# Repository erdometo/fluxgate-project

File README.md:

# 🧲 High-Precision Fluxgate Magnetic Field Sensor Design

An open-source, high-sensitivity, single-axis Fluxgate magnetometer and development platform designed for aerospace, geophysics, and navigation applications. This project implements a fully integrated system containing hardware (KiCad PCBs), firmware (MSP430 24-bit SD-ADC & RP2040 Controller), simulations (LTSpice), and software (Python PyQt real-time GUI).

Developed as a senior capstone engineering project at **Karadeniz Technical University (KTU)** by **Erdem Metin** and **Mücahit Ata**, under the supervision of **Prof. Dr. İsmail Kaya**.

---

## 📸 System Overview

The Fluxgate sensor system is designed around a dual-MCU architecture consisting of an **RP2040** (master controller and driver) and an **MSP430AFE253** (24-bit Sigma-Delta ADC data acquisition).

*Fig 1: Full system schematic diagram detailing all MCU pinouts, power distribution, and analog filters.*

*Fig 2: KiCad PCB 3D layout render (left) and the fully assembled physical testing board (right).*

```mermaid
graph TD
    PC[Computer PyQt GUI / Matlab] <-->|USB virtual COM / UDP Wifi| Pico[Raspberry Pi Pico RP2040]
    Pico -->|PWM Excitation Control f| FET[H-Bridge MOSFET Driver]
    FET -->|AC Excitation staircase Wave| Core[Magnetic Core & Coils]
    Core -->|Induced Sensing Signal| Demod[Analog Processing Circuit]
    Demod -->|DC Level / AC Signal| MSP[MSP430AFE253 24-bit ADC]
    MSP -->|1.5 MBaud UART| Pico
```

---

## 📖 Theory of Operation

A **Fluxgate Magnetometer** measures weak static or low-frequency magnetic fields (in the nT to µT range) by exploiting the non-linear magnetic saturation characteristics of a ferromagnetic core.

1. **Excitation (Drive):** An AC current at frequency $f$ drives the core deep into saturation in both positive and negative directions.
2. **Symmetric Core State:** In the absence of an external magnetic field, the magnetic flux changes symmetrically. The voltage induced in the sensing (pick-up) coil contains only **odd harmonics** ($3f$, $5f$, etc.).
3. **Asymmetric Core State (External Field Present):** When an external magnetic field (like the Earth's field $H_{ext}$) is present, it biases the core, causing it to saturate earlier in one direction and later in the other.
4. **Second Harmonic (2f) Detection:** This asymmetry generates **even harmonics** (predominantly the $2f$ component) in the sensing coil. The amplitude of this second harmonic is directly proportional to the magnitude of the external magnetic field, and its phase indicates the field's direction.

---

## 🛠️ Project Structure

The repository is structured into logically separated folders to make implementation and replication straightforward:

*   📁 **[`Hardware/`](file:///c:/Users/ASUS/Desktop/Fluxgate/Fluxgate-Project-Files/Hardware)**: KiCad schematic and PCB layout designs, Gerber files, and Bill of Materials (BOM).
*   📁 **[`Firmware/`](file:///c:/Users/ASUS/Desktop/Fluxgate/Fluxgate-Project-Files/Firmware)**:
    *   **MSP430:** IAR and CCS projects for 24-bit Sigma-Delta ADC sampling at 16.5 kSps and 1.5 MBaud USART transmission.
    *   **RP2040 (Raspberry Pi Pico):** C/C++ SDK projects generating precise excitation PWM and streaming data to PC via USB Serial or UDP Wi-Fi.
*   📁 **[`Software/`](file:///c:/Users/ASUS/Desktop/Fluxgate/Fluxgate-Project-Files/Software)**: Python-based GUI utilizing `pyqtgraph` for real-time serial and UDP plotting, and Matlab analytics.
*   📁 **[`Simulations/`](file:///c:/Users/ASUS/Desktop/Fluxgate/Fluxgate-Project-Files/Simulations)**: LTSpice circuits simulating the H-Bridge excitation driver and the analog synchronous demodulation path.

---

## 🚀 Step-by-Step Build & Replication Guide

To replicate and build this high-precision Fluxgate sensor, follow these five steps:

### 1. Hardware Fabrication & Assembly
1. Go to **[`Hardware/`](file:///c:/Users/ASUS/Desktop/Fluxgate/Fluxgate-Project-Files/Hardware)** and select either the **Excitation Circuit V1**, the **Excitation Circuit Final**, or the **JLCPCB Version** which is optimized for SMT assembly.
2. Export Gerbers or use the provided `.zip` files under the directories to order PCBs from your manufacturer (e.g., JLCPCB).
3. Assemble the PCB using the BOM. Key components include:
    *   **Primary Controller:** Raspberry Pi Pico (RP2040)
    *   **Precision ADC:** MSP430AFE253IPW (24-bit Sigma-Delta ADC)
    *   **H-Bridge Driver:** HIP4082xB half-bridge gate driver
    *   **Excitation MOSFETs:** AP2300 or IRFZ44N
    *   **Ultra Low-Noise Opamps:** TP2311 or LT149x series (12nV/√Hz input noise)
    *   **Voltage References:** AN431 shunt regulators (2.5V, 20ppm/°C stability)

### 2. Fluxgate Core & Coil Preparation
1. **Core Selection:** Use a high-permeability **green iron-powder ferrite toroid core** with an **inner diameter of 7 mm, thickness of 2 mm, and height of 4.5 mm**. (While a 6-81 Permalloy racetrack core with $100\text{ µm}$ laminations provides lower noise, a toroidal ferrite core is robust and hand-windable).
2. **Drive Winding:** Wind the excitation (drive) coil uniformly around the toroid using **32 AWG** enameled copper wire. In the experimental prototype, the completed drive winding exhibited a measured **series resistance of $17.945\text{ }\Omega$** and a **series inductance of $19.686\text{ mH}$**.
3. **Sense Winding:** Wind the sensing (pick-up) coil on top of the drive winding, orienting the windings to capture the fluxgate effect while canceling direct coupling from the excitation drive.

*Fig 3: The custom hand-wound toroidal fluxgate core integrated onto the testing board.*

### 3. Simulation & Validation
1. Open **[`Simulations/LTSpice/`](file:///c:/Users/ASUS/Desktop/Fluxgate/Fluxgate-Project-Files/Simulations)**.
2. Run `fluxgate.asc` to simulate the H-Bridge excitation path. Verify the staircase voltage waveform across the drive bobbin.
3. Run `fluxgateACAnaliz.asc` or `Draft7.asc` to analyze the frequency response of the active integrator and synchronous demodulator. Ensure the integration region lies between **159 Hz and 1591 Hz** and the low-pass filter kesim frekansı is configured near **28 Hz**.

### 4. Firmware Deployment
1. **MSP430 Firmware:**
    *   Open IAR Embedded Workbench or Code Composer Studio.
    *   Load the project in **[`Firmware/MSP430_AFE_ADC/`](file:///c:/Users/ASUS/Desktop/Fluxgate/Fluxgate-Project-Files/Firmware/MSP430_AFE_ADC)** or **[`Firmware/MSP430_ADC_to_UART/`](file:///c:/Users/ASUS/Desktop/Fluxgate/Fluxgate-Project-Files/Firmware/MSP430_ADC_to_UART)**.
    *   Compile and flash the firmware using an eZ-FET debugger (or the Spy-Bi-Wire pins on an MSP430 Launchpad).
    *   *Function:* Configures the 12MHz MCLK, initializes the SD24 Module in group conversion mode, and streams 24-bit raw ADC readings via USART0 at **1.5M Baud**.
2. **RP2040 Firmware:**
    *   Navigate to **[`Firmware/Pico_Firmwares/`](file:///c:/Users/ASUS/Desktop/Fluxgate/Fluxgate-Project-Files/Firmware/Pico_Firmwares)**.
    *   Choose either `pico-custom-firmware-usb` (USB Virtual Serial) or `pico-custom-firmware-udp` (Wi-Fi streaming).
    *   Build the project using the Pico SDK (`CMake`) and flash the resulting `.uf2` file onto your Pi Pico.
    *   *Function:* Emits precise complementary PWM drive signals (80µs duty, 40µs dead-time) at frequency $f$ to drive the H-Bridge. It uses a **PIO state machine** to reliably capture the 1.5MBaud UART stream from the MSP430 and forwards it to the PC.

### 5. GUI & Visualization
1. Install Python 3 and requirements:
   ```bash
   pip install pyqtgraph PyQt5 pyserial numpy
   ```
2. Run the visualization app in **[`Software/Python_GUI_Demo/`](file:///c:/Users/ASUS/Desktop/Fluxgate/Fluxgate-Project-Files/Software/Python_GUI_Demo)**:
   ```bash
   python compass.py
   # or
   python pyqtgraph_float_v2x2_yesim.py
   ```
3. Connect your Pi Pico to the PC via USB. You will see a real-time rolling graph of the 24-bit sampled magnetic field data representing the external field.

---

## 📡 Digital Signal Processing (DSP) & Digital Lock-In Mode

During the final experimental testing phase of this project, the analog op-amps in the physical synchronous demodulation circuit were found to be defective or counterfeit, preventing analog phase detection from working out of the box. To solve this, the project utilized a highly robust **Digital Signal Processing (DSP)** pipeline to bypass the analog demodulator entirely.

### Bypassing the Analog Demodulator
1. The analog SPDT switch (SN74LVC1G3157) was disabled (tied to a static ground state via the MCU).
2. The active low-noise op-amps were configured as a simple differential preamplifier.
3. The raw, high-speed AC signal (which contains the even and odd harmonics) was fed directly into the **MSP430's 24-bit Sigma-Delta ADC**.
4. The raw, un-demodulated samples were digitized at ~16.5 kSps and streamed to the PC via the RP2040 UART/USB bridge.

### Two Host-Side Digital Processing Implementations
Your software repository implements two distinct mathematical approaches on the host PC to extract the external magnetic field from this raw stream:

1. **Frequency-Domain Demodulation (Real-Time FFT):**
   * *File:* **[`pyqtgraph_float_v2x2_yesim.py`](file:///c:/Users/ASUS/Desktop/Fluxgate/Fluxgate-Project-Files/Software/Python_GUI_Demo/pyqtgraph_float_v2x2_yesim.py)**
   * *Method:* Computes a high-performance **Fast Fourier Transform (FFT)** on blocks of 8192 raw samples using Scipy:
     ```python
     Yf0 = fft(ch0)
     ```
   * *Result:* The GUI displays the real-time frequency spectrum. By measuring the amplitude peak of the **second harmonic ($2f$ at 25 kHz)** in the frequency domain, the software calculates the precise external magnetic field intensity, completely replacing the physical analog lock-in filters!

2. **Time-Domain Smoothing (Moving Average Convolution):**
   * *Files:* **[`udp_plot_pyqt.py`](file:///c:/Users/ASUS/Desktop/Fluxgate/Fluxgate-Project-Files/Software/Python_GUI_Demo/udp_plot_pyqt.py)** and **[`udp_plot_pyqt_2.py`](file:///c:/Users/ASUS/Desktop/Fluxgate/Fluxgate-Project-Files/Software/Python_GUI_Demo/udp_plot_pyqt_2.py)**
   * *Method:* Unpacks the high-speed telemetry and applies a real-time **Moving Average Filter** using NumPy convolution across a 1000-sample window:
     ```python
     filtered_data = np.convolve(data, weights, mode='valid')
     ```
   * *Result:* Smooths out the excitation switching ripples and transient spikes, feeding a clean time-domain signal to the graphical compass needle interface to dynamically show the core's magnetic orientation.

---

## 🛠️ Hardware Debugging & Engineering Solutions

During the assembly and testing phase, two critical engineering challenges arose and were systematically resolved:

### 1. The H-Bridge Bootstrap Capacitor & Duty Cycle Adaptation
*   **The Issue:** High-side gate drivers require a bootstrap capacitor ($C_{Bst}$) to maintain the gate-to-source voltage ($V_{GS}$) when the high-side MOSFET turns on. By design guidelines, the minimum bootstrap capacitance is:
    $$C_{Bst} = \frac{Q_{gate}}{\Delta V_{Bst}}$$
    Using the AP2300 gate charge $Q_{gate} = 11\text{ nC}$ and an acceptable voltage ripple $\Delta V_{Bst} = 0.1\text{ V}$, the minimum capacitor required is $110\text{ nF}$. Due to a design oversight, a **$1\text{ nF}$** capacitor was initially populated. This capacitor discharged instantly, causing the high-side gate drivers to drop out immediately.
*   **The Fix:** Populating a **$1\text{ µF}$** capacitor resolved the gate-dropout issue. However, experimental tests under a $330\text{ }\Omega$ load revealed that the high-side gate could remain continuously open for a maximum of **$1.125\text{ ms}$** before the bootstrap charge depleted.
*   **PWM Adaptation:** To prevent the high-side gate from collapsing during lower frequencies, the RP2040 firmware was adapted to emit a highly optimized PWM excitation pattern. Instead of a basic symmetrical square wave, the drive cycle was structured as:
    *   **$0.8\text{ ms}$ Positive Drive Phase** (containing high-speed $80\text{ µs}$ pulses with $40\text{ µs}$ dead-times).
    *   **$0.4\text{ ms}$ Neutral Phase** (H-bridge disabled, allowing the bootstrap capacitors to fully recharge).
    *   **$0.8\text{ ms}$ Negative Drive Phase** (H-bridge reversed).

### 2. Defective Analog Op-Amps & DSP Bypass
*   **The Issue:** During board validation, short-circuiting the sensing coil to ground resulted in the low-noise differential preamplifier and active integrator output locks stuck at a solid **$2.5\text{ V}$** (the virtual ground analog reference voltage). The op-amps (TP2311 or LT1492) failed to respond to any AC or DC input signal changes, leading to the conclusion that the physical components received were defective or counterfeit.
*   **The Solution:** The analog synchronous SPDT demodulator switch (SN74LVC1G3157) was set to ground mode via the RP2040, transforming the first stage into a simple, highly linear $1:2$ differential preamplifier (total differential gain of 20). The raw, high-speed AC pick-up signal was routed directly into the MSP430's 24-bit Sigma-Delta ADC, and the entire lock-in and filtering cascade was bypassed in hardware and reconstructed in real-time software on the host PC.

---

## ⚡ Specifications

| Parameter | Value | Description |
| :--- | :--- | :--- |
| **Sensor Type** | Parallel Fluxgate | Single Axis Magnetometer |
| **Excitation Waveform** | AC Staircase Wave | Minimizes transient EMF spikes |
| **Excitation Frequency** | 12.5 kHz | Configurable via Pico PWM registers |
| **ADC Resolution** | 24-Bit | Sigma-Delta Converter (MSP430AFE253) |
| **Sampling Rate** | ~16,500 samples/sec | High-speed oversampled stream |
| **Baud Rate** | 1,500,000 Baud | High-speed MSP430 to RP2040 UART link |
| **Demodulator Gain** | 1:10 (or 20 Differential) | Synchronous analog SPDT demodulation |
| **Low-Pass Filter (LPF)** | $f_c = 28.42\text{ Hz}$ | Eliminates grid noise (50Hz) and ripples |
| **Integrator Bandwidth** | 159 Hz to 1591 Hz | Limits noise and captures second harmonics |

---

## ⚖️ License

This project is open-source and released under the [MIT License](file:///c:/Users/ASUS/Desktop/Fluxgate/Fluxgate-Project-Files/LICENSE). Feel free to use, modify, and distribute for personal, academic, or commercial purposes.

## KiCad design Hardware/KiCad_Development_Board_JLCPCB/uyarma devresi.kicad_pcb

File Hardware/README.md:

# 🔌 Hardware & PCB Design

This folder contains the KiCad schematics and PCB layout files for the Fluxgate Sensor Development and Testing Board. The hardware combines the master controller, excitation power electronics, high-speed 24-bit ADC, and a low-noise analog signal processing path into a single 150mm x 100mm PCB.

*Fig 1: Complete circuit schematic for the Fluxgate Development Board (open-source).*

*Fig 2: KiCad board layout 3D render (left) and the actual manufactured PCB received from JLCPCB (right).*

---

## 📁 Directory Directory

*   📁 **[`Excitation_Circuit_V1/`](file:///c:/Users/ASUS/Desktop/Fluxgate/Fluxgate-Project-Files/Hardware/Excitation_Circuit_V1)**: The initial KiCad prototype.
*   📁 **[`Excitation_Circuit_Final/`](file:///c:/Users/ASUS/Desktop/Fluxgate/Fluxgate-Project-Files/Hardware/Excitation_Circuit_Final)**: The revised KiCad project with improvements in the bootstrap driver and ground isolation.
*   📁 **[`KiCad_Development_Board_JLCPCB/`](file:///c:/Users/ASUS/Desktop/Fluxgate/Fluxgate-Project-Files/Hardware/KiCad_Development_Board_JLCPCB)**: Design optimized for JLCPCB's automated surface mount technology (SMT) assembly service. Contains BOM and component positioning files.

---

## ⚡ Hardware Architecture & Circuit Sub-systems

The Fluxgate Development Board contains four main hardware sub-systems:

### 1. Power Management & Low-Noise Rails
Since magnetic sensors are highly sensitive to power supply noise, a robust voltage regulation and reference system is implemented:
*   **Main Regulator:** AMS1117-3.3 produces the digital 3.3V supply.
*   **Negative Rail Generator:** ME7660C charge-pump voltage converter generates a low-noise $-3.3\text{ V}$ rail from the $3.3\text{ V}$ input.
*   **Precision Analog References:** Originally, the op-amps shared the noisy 3.3V digital rail with the microcontrollers, which coupled massive MCU switching ripples into the analog signal path. To achieve extremely low-noise operation, the board was modified to use two **AN431 precision shunt regulators** with a **20 PPM/°C temperature coefficient**. These regulators derive highly stable $+2.5\text{ V}$ and $-2.5\text{ V}$ virtual ground references from the noisy $3.3\text{ V}$ rail, isolated via $10\text{ }\Omega$ current-limiting resistors to prevent temperature-induced offset drifts.

```
       [ 5V USB Input ]
              │
      ┌───────┴───────┐
      ▼               ▼
[AMS1117-3.3V]   [ME7660C]
      │               │
  [ +3.3V ]       [ -3.3V ]
      │               │
  [ AN431 ]       [ AN431 ]
      │               │
  [ +2.5V ]       [ -2.5V ]
```

### 2. Excitation Drive (H-Bridge)
To saturate the ferromagnetic core in both directions:
*   **Drivers:** Two half-bridge drivers (LP1111) are configured to form a full H-bridge.
*   **Switching Elements:** Low $R_{DS(on)}$ AP2300 or IRFZ44N N-channel MOSFETs.
*   **Protection:** 1N5400 flyback diodes protect the MOSFETs against massive back-EMF spikes (up to 200A instantaneous rating) when the coil current reverses.
*   **Bootstrap Optimization:** High-side gate drivers require a bootstrap capacitor ($C_{Bst}$) to maintain the gate-to-source voltage ($V_{GS}$) when the high-side MOSFET is active. The minimum bootstrap capacitance is calculated using:
    $$C_{Bst} = \frac{Q_{gate}}{\Delta V_{Bst}}$$
    Using the AP2300 gate charge $Q_{gate} = 11\text{ nC}$ and an acceptable voltage ripple $\Delta V_{Bst} = 0.1\text{ V}$, the minimum capacitor required is $110\text{ nF}$.
    *   Due to a design oversight, a **$1\text{ nF}$** capacitor was initially populated, causing the high-side MOSFETs to fail to switch completely.
    *   Replacing this with a **$94\text{ nF}$** capacitor allowed switching but triggered rapid charge depletion, causing the gates to turn on and off hundreds of times during a 5ms cycle.
    *   Restoring this to **$1\text{ µF}$** in the final hardware stabilized the gate, allowing stable gate-on periods up to **$1.125\text{ ms}$** under a $330\text{ }\Omega$ load.

### 3. Low-Noise Analog Signal Processing
The induced voltage from the pickup (sensing) coil undergoes analog preprocessing to extract the second harmonic component ($2f$):
*   **Differential Input Preamp:** Winding coupling experiences massive Common-Mode coupling from the high-voltage excitation drive. To solve this, the sensing coil is connected to a **differential preamplifier with a 1:2 gain** using low-noise TP2311 or LT1492 op-amps. This rejects common-mode excitation noise while increasing the differential sensing signal, bringing the total channel gain to 20.
*   **Synchronous Demodulator:** An SN74LVC1G3157 analog SPDT switch acts as a phase-sensitive rectifier. It is toggled by the RP2040 at twice the excitation frequency ($2f$), demodulating the second harmonic directly to DC.
*   **Active Integrator:** A low-pass integrator with an integration bandwidth configured between **159 Hz and 1591 Hz** ($\text{BW} = 1/(2\pi R_f C)$ with $R_f = 100\text{ k}\Omega, C = 10\text{ nF}$).
*   **Output Filter:** An RC low-pass filter with a cutoff frequency $f_c = 28.42\text{ Hz}$ ($C = 100\text{ nF}, R = 56\text{ k}\Omega$) filters out the $50\text{ Hz}$ mains grid noise and lingering switching ripples.

### 4. Precision Digitization & Processing
*   **MSP430AFE253:** Reads the filtered DC level (or the pre-demodulated high-speed AC signal) using its internal **24-bit Sigma-Delta ADC**. It runs on a $12\text{ MHz}$ internal DCO and transmits over UART at **1.5M Baud**.
*   **RP2040 (Raspberry Pi Pico):** Controls H-Bridge timing and routes the MSP430's digitized telemetry to a computer via USB virtual serial or a UDP socket over Wi-Fi.

---

## 📋 Component Checklist (BOM)

If assembling the board manually, ensure the following core components are ready:

| Designator | Component Name | Package | Description |
| :--- | :--- | :--- | :--- |
| **U5** | Raspberry Pi Pico | Module | Master controller and PWM driver |
| **U4** | MSP430AFE253IPW | TSSOP-24 | 24-Bit Sigma-Delta ADC / High-Speed DSP |
| **U1, U2** | LP1111 (or HIP4082) | SOIC-8 | Half-Bridge Bootstrap MOSFET Gate Drivers |
| **Q1 - Q4** | AP2300 (or IRFZ44N) | SOT-23 / TO-220 | Excitation H-Bridge Switching MOSFETs |
| **U3, U8, U9** | TP2311 (or LT1492) | SOIC-8 | $12\text{ nV}/\sqrt{\text{Hz}}$ Low-Noise Precision Op-Amps |
| **U12** | SN74LVC1G3157 | SOT-363 | High-Speed SPDT Analog Switch (Demodulator) |
| **U10, U11** | AN431 | SOT-23 | High-Precision Shunt Voltage Regulator (2.5V) |
| **U6** | ME7660C | SOIC-8 | Switched-Capacitor Negative Voltage Converter |
| **U7** | AMS1117-3.3 | SOT-223 | $3.3\text{ V}$ Low-Dropout Linear Regulator |
| **D1 - D4** | 1N5400 (or 1N4148) | DO-201AD | 200A Flyback Back-EMF Protection Diodes |

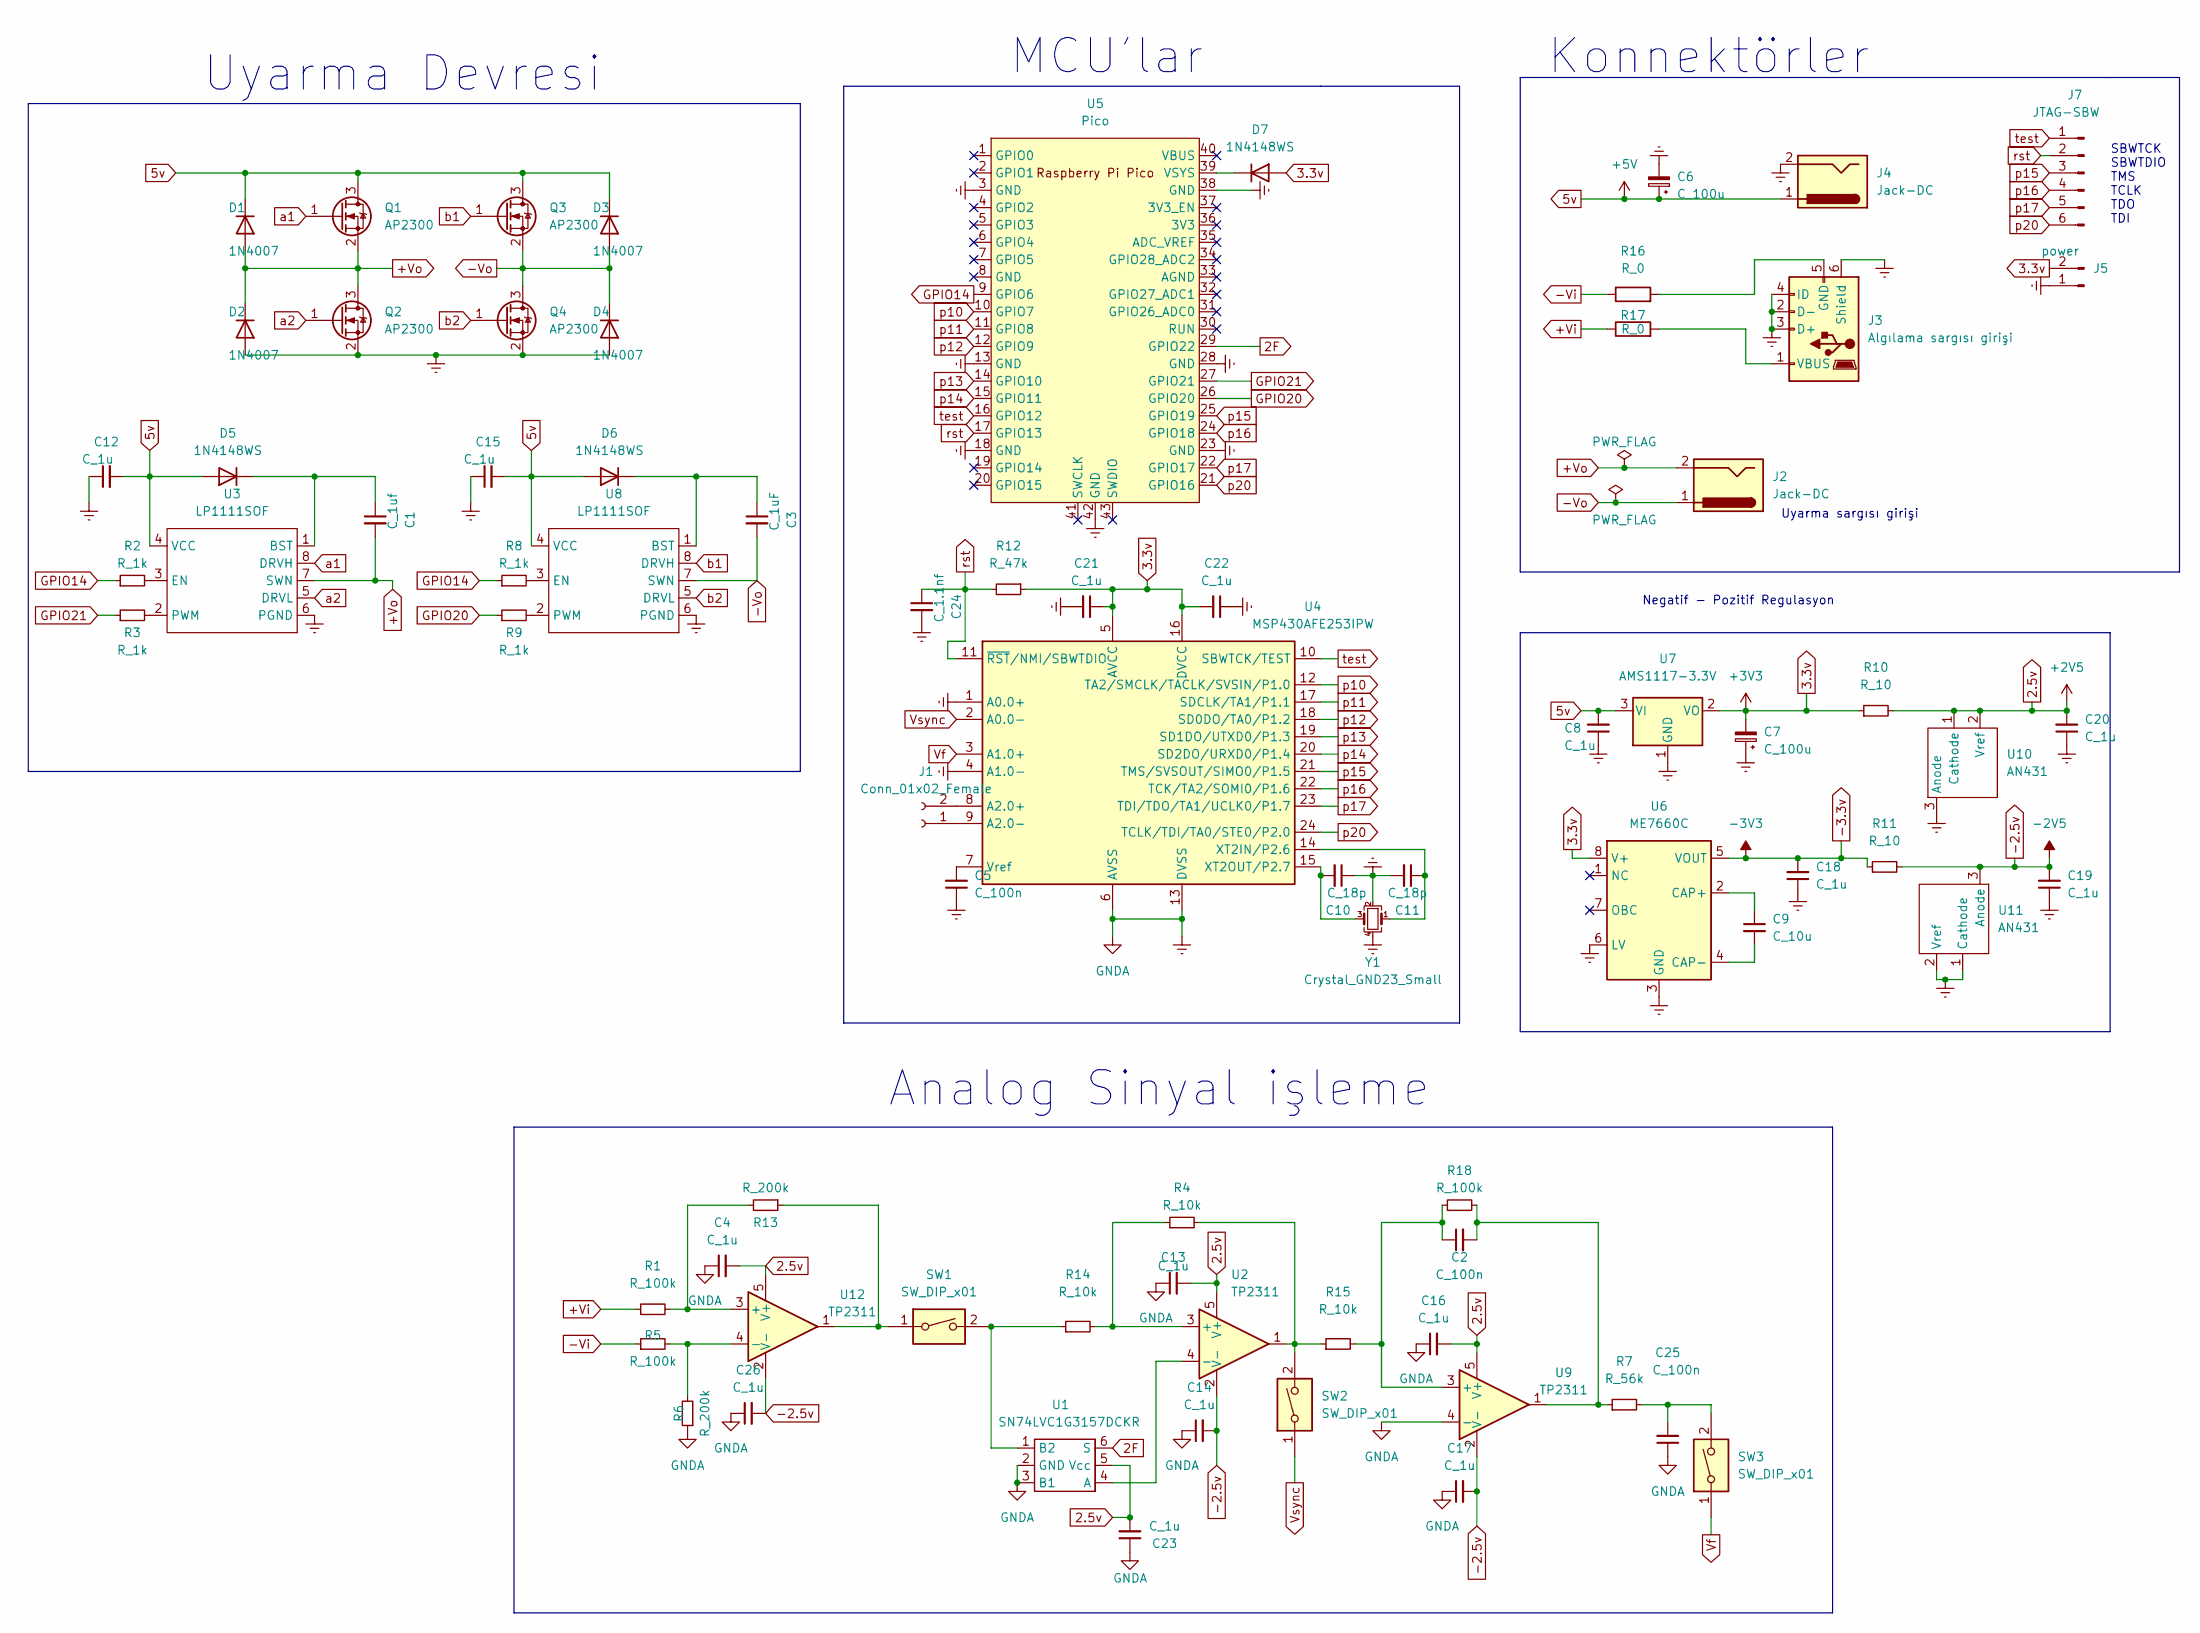
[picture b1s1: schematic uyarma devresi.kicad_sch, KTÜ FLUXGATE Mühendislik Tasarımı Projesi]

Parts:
C1: C_1uf; C_0402_1005Metric
C2, C5, C25: C_100n; C_0402_1005Metric
C3: C_1uF; C_0402_1005Metric
C4, C8, C12, C13, C14, C15, C16, C17, C18, C19, C20, C21, C22, C23, C26: C_1u; C_0402_1005Metric
C6, C7: C_100u; C_1206_3216Metric
C9: C_10u; C_0402_1005Metric
C10, C11: C_18p; C_0402_1005Metric
C24: C_1.1nf; C_0402_1005Metric
D1, D2, D3, D4: 1N4007; D_SOD-123F
D5, D6, D7: 1N4148WS; D_SOD-323
J1: Conn_01x02_Female; PinHeader_1x02_P2.54mm_Vertical
J2, J4: Jack-DC; BarrelJack_GCT_DCJ200-10-A_Horizontal
J3: Algılama sargısı girişi; USB_Micro-B_Molex-105017-0001
J5: power; PinHeader_1x02_P2.54mm_Vertical
J7: JTAG-SBW; PinHeader_1x06_P2.54mm_Vertical
Q1, Q2, Q3, Q4: AP2300; TSOT-23
R1, R5, R18: R_100k; R_0402_1005Metric
R2, R3, R8, R9: R_1k; R_0402_1005Metric
R4, R14, R15: R_10k; R_0402_1005Metric
R6, R13: R_200k; R_0402_1005Metric
R7: R_56k; R_0402_1005Metric
R10, R11: R_10; R_1206_3216Metric
R12: R_47k; R_0402_1005Metric
R16, R17: R_0; R_1206_3216Metric
SW1, SW2, SW3: SW_DIP_x01; SW_DIP_SPSTx01_Slide_6.7x4.1mm_W7.62mm_P2.54mm_LowProfile
U1: SN74LVC1G3157DCKR; Texas_R-PDSO-G6
U2, U9, U12: TP2311; SOT-23-5
U3, U8: LP1111SOF; SOP-8-1EP_4.57x4.57mm_P1.27mm_EP4.57x4.45mm
U4: MSP430AFE253IPW; TSSOP-24_4.4x7.8mm_P0.65mm
U5: Pico; RPi_Pico_SMD_TH
U6: ME7660C; SOP-8-1EP_4.57x4.57mm_P1.27mm_EP4.57x4.45mm
U7: AMS1117-3.3V; SOT-223-3_TabPin2
U10, U11: AN431; SOT-23
Y1: Crystal_GND23_Small; Crystal_SMD_3225-4Pin_3.2x2.5mm

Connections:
2.5v: C4.2, C13.2, C16.2, C20.2, C23.2, R10.2, U1.5 (Vcc), U2.5 (V+), U9.5 (V+), U10.1 (Cathode), U10.2 (Vref), U12.5 (V+)
2F: U1.6 (S), U5.29 (GPIO22)
3.3v: C7.2, C21.1, C22.2, D7.2 (A), J5.2, R10.1, R12.1, U4.5 (AVCC), U4.16 (DVCC), U6.8 (V+), U7.2 (VO)
5v: C6.1, C8.2, C12.2, C15.2, D1.1 (K), D3.1 (K), D5.2 (A), D6.2 (A), J4.1, Q1.3 (D), Q3.3 (D), U3.4 (VCC), U7.3 (VI), U8.4 (VCC)
+Vi: R1.1, R17.1
+Vo: C1.2, D1.2 (A), D2.1 (K), J2.2, Q1.2 (S), Q2.3 (D), U3.7 (SWN)
-2.5v: C14.2, C17.2, C19.2, C26.2, R11.2, U2.2 (V-), U9.2 (V-), U11.3 (Anode), U12.2 (V-)
-3.3v: C18.2, R11.1, U6.5 (VOUT)
-Vi: R5.1, R16.1
-Vo: C3.2, D3.2 (A), D4.1 (K), J2.1, Q3.2 (S), Q4.3 (D), U8.7 (SWN)
Earth: C4.1, C5.1, C6.2, C7.1, C8.1, C10.1, C11.2, C12.1, C13.1, C14.1, C15.1, C16.1, C17.1, C18.1, C19.1, C20.1, C21.2, C22.1, C23.1, C24.2, C25.1, C26.1, D2.2 (A), D4.2 (A), J3.2 (D-), J3.3 (D+), J3.4 (ID), J3.6 (Shield), J4.2, J5.1, Q2.2 (S), Q4.2 (S), R6.1, U1.2 (GND), U1.3 (B1), U3.6 (PGND), U4.1 (A0.0+), U4.4 (A1.0-), U4.6 (AVSS), U4.13 (DVSS), U5.3 (GND), U5.13 (GND), U5.18 (GND), U5.23 (GND), U5.28 (GND), U5.38 (GND), U5.42 (GND), U6.3 (GND), U6.6 (LV), U7.1 (GND), U8.6 (PGND), U9.4 (-), U10.3 (Anode), U11.1 (Cathode), U11.2 (Vref), Y1.2, Y1.4
GPIO14: R2.1, R8.1, U5.9 (GPIO6)
GPIO20: R9.1, U5.26 (GPIO20)
GPIO21: R3.1, U5.27 (GPIO21)
unnamed: C1.1, D5.1 (K), U3.1 (BST)
unnamed: C2.1, R15.2, R18.1, U9.3 (+)
unnamed: C2.2, R7.1, R18.2, U9.1
unnamed: C3.1, D6.1 (K), U8.1 (BST)
unnamed: C5.2, U4.7 (Vref)
unnamed: C9.1, U6.2 (CAP+)
unnamed: C9.2, U6.4 (CAP-)
unnamed: C10.2, U4.15 (XT2OUT/P2.7), Y1.3
unnamed: C11.1, U4.14 (XT2IN/P2.6), Y1.1
unnamed: C25.2, R7.2, SW3.2
unnamed: J1.1, U4.9 (A2.0-)
unnamed: J1.2, U4.8 (A2.0+)
unnamed: J3.1 (VBUS), R17.2
unnamed: J3.5 (GND), R16.2
unnamed: R1.2, R13.2, U12.3 (+)
unnamed: R2.2, U3.3 (EN)
unnamed: R3.2, U3.2 (PWM)
unnamed: R4.1, R14.2, U2.3 (+)
unnamed: R4.2, R15.1, SW2.2, U2.1
unnamed: R5.2, R6.2, U12.4 (-)
unnamed: R8.2, U8.3 (EN)
unnamed: R9.2, U8.2 (PWM)
unnamed: R13.1, SW1.1, U12.1
unnamed: R14.1, SW1.2, U1.1 (B2)
unnamed: U1.4 (A), U2.4 (-)
unnamed: D7.1 (K), U5.39 (VSYS)
Vf: SW3.1, U4.3 (A1.0+)
Vsync: SW2.1, U4.2 (A0.0-)
a1: Q1.1 (G), U3.8 (DRVH)
a2: Q2.1 (G), U3.5 (DRVL)
b1: Q3.1 (G), U8.8 (DRVH)
b2: Q4.1 (G), U8.5 (DRVL)
p10: U4.12 (TA2/SMCLK/TACLK/SVSIN/P1.0), U5.10 (GPIO7)
p11: U4.17 (SDCLK/TA1/P1.1), U5.11 (GPIO8)
p12: U4.18 (SD0DO/TA0/P1.2), U5.12 (GPIO9)
p13: U4.19 (SD1DO/UTXD0/P1.3), U5.14 (GPIO10)
p14: U4.20 (SD2DO/URXD0/P1.4), U5.15 (GPIO11)
p15: J7.3, U4.21 (TMS/SVSOUT/SIMO0/P1.5), U5.25 (GPIO19)
p16: J7.4, U4.22 (TCK/TA2/SOMI0/P1.6), U5.24 (GPIO18)
p17: J7.5, U4.23 (TDI/TDO/TA1/UCLK0/P1.7), U5.22 (GPIO17)
p20: J7.6, U4.24 (TCLK/TDI/TA0/STE0/P2.0), U5.21 (GPIO16)
rst: C24.1, J7.2, R12.2, U4.11 (~RST/NMI/SBWTDIO), U5.17 (GPIO13)
test: J7.1, U4.10 (SBWTCK/TEST), U5.16 (GPIO12)

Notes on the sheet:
Uyarma sargısı girişi
Analog Sinyal işleme
MCU'lar
SBWTCK SBWTDIO TMS TCLK TDO TDI
Negatif - Pozitif Regulasyon
Uyarma Devresi
Konnektörler

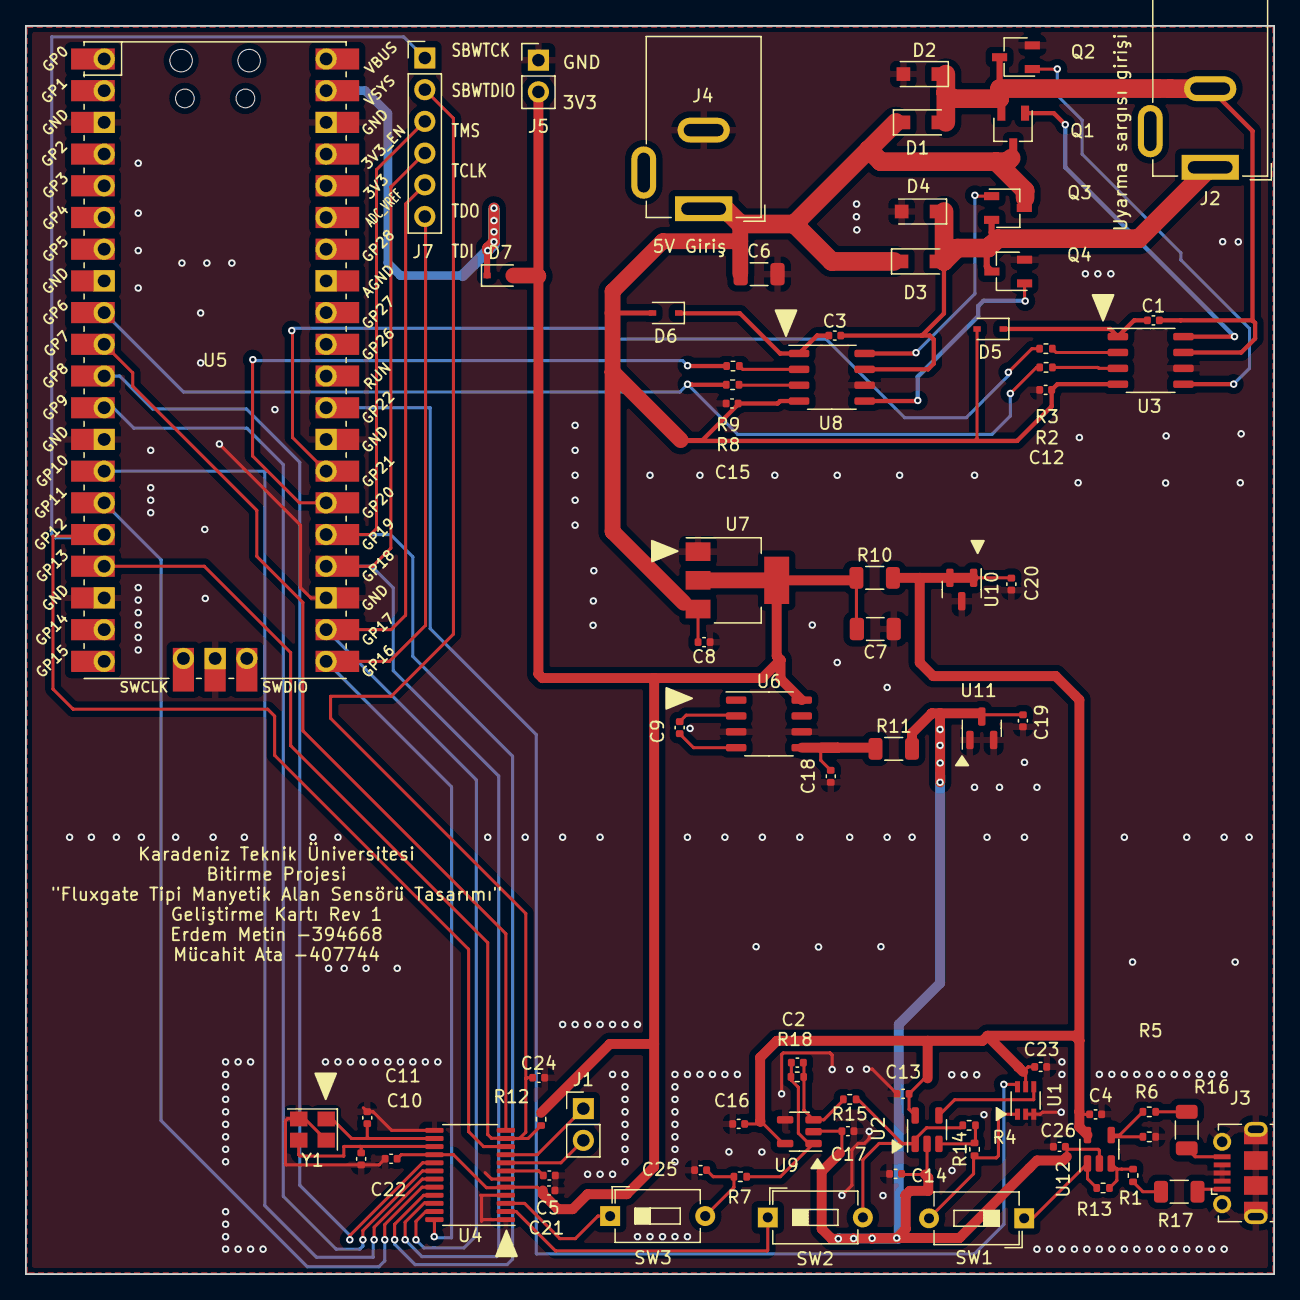
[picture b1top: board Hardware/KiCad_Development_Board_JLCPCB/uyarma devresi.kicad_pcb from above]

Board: 2 copper layers, 100.0 x 100.0 mm, 77 parts (0 on the bottom side), 57 nets.

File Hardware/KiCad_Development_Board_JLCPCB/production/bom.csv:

Designator,Footprint,Quantity,Value,LCSC Part #
C1,0402,1,C_1.1nf,
C10,0402,1,C_18p,
C11,0402,1,C_18p,
C12,0402,1,C_1u,
C13,0402,1,C_1u,
C14,0402,1,C_1u,
C15,0402,1,C_1u,
C16,0402,1,C_1u,
C17,0402,1,C_1u,
C18,0402,1,C_1u,
C19,0402,1,C_1u,
C2,0402,1,C_100n,
C20,0402,1,C_1u,
C21,0402,1,C_1u,
C22,0402,1,C_1u,
C23,0402,1,C_1u,
C24,0402,1,C_1.1nf,
C25,0402,1,C_100n,
C26,0402,1,C_1u,
C3,0402,1,C_1.1nf,
C4,0402,1,C_1u,
C5,0402,1,C_100n,
C6,1206,1,C_100u,
C7,1206,1,C_100u,
C8,0402,1,C_1u,
C9,0402,1,C_10u,
"D1, D2, D3, D4",D_SOD-123F,4,1N4007,
"D5, D6, D7",D_SOD-323,3,1N4148WS,
J1,PinHeader_1x02_P2.54mm_Vertical,1,Conn_01x02_Female,
"J2, J4",BarrelJack_GCT_DCJ200-10-A_Horizontal,2,Jack-DC,
J3,USB_Micro-B_Molex-105017-0001,1,Algılama sargısı girişi,
J5,PinHeader_1x02_P2.54mm_Vertical,1,power,
J7,PinHeader_1x06_P2.54mm_Vertical,1,JTAG-SBW,
"Q1, Q2, Q3, Q4",TSOT-23,4,AP2300,
R1,0402,1,R_100k,
R10,1206,1,R_10,
R11,1206,1,R_10,
R12,0402,1,R_47k,
R13,0402,1,R_200k,
R14,0402,1,R_10k,
R15,0402,1,R_10k,
R16,1206,1,R_0,
R17,1206,1,R_0,
R18,0402,1,R_100k,
R2,0402,1,R_1k,
R3,0402,1,R_1k,
R4,0402,1,R_10k,
R5,0402,1,R_100k,
R6,0402,1,R_200k,
R7,0402,1,R_56k,
R8,0402,1,R_1k,
R9,0402,1,R_1k,
"SW1, SW2, SW3",SW_DIP_SPSTx01_Slide_6.7x4.1mm_W7.62mm_P2.54mm_LowProfile,3,SW_DIP_x01,
U1,Texas_R-PDSO-G6,1,SN74LVC1G3157DCKR,
"U10, U11",SOT-23,2,AN431,
"U12, U2, U9",SOT-23-5,3,TP2311,
"U3, U8",SOP-8_3.9x4.9mm_P1.27mm,2,LP1111SOF,
U4,TSSOP-24_4.4x7.8mm_P0.65mm,1,MSP430AFE253IPW,
U5,RPi_Pico_SMD_TH,1,Pico,
U6,SOP-8_3.9x4.9mm_P1.27mm,1,ME7660C,
U7,SOT-223-3_TabPin2,1,AMS1117-3.3V,
Y1,Crystal_SMD_3225-4Pin_3.2x2.5mm,1,Crystal_GND23_Small,

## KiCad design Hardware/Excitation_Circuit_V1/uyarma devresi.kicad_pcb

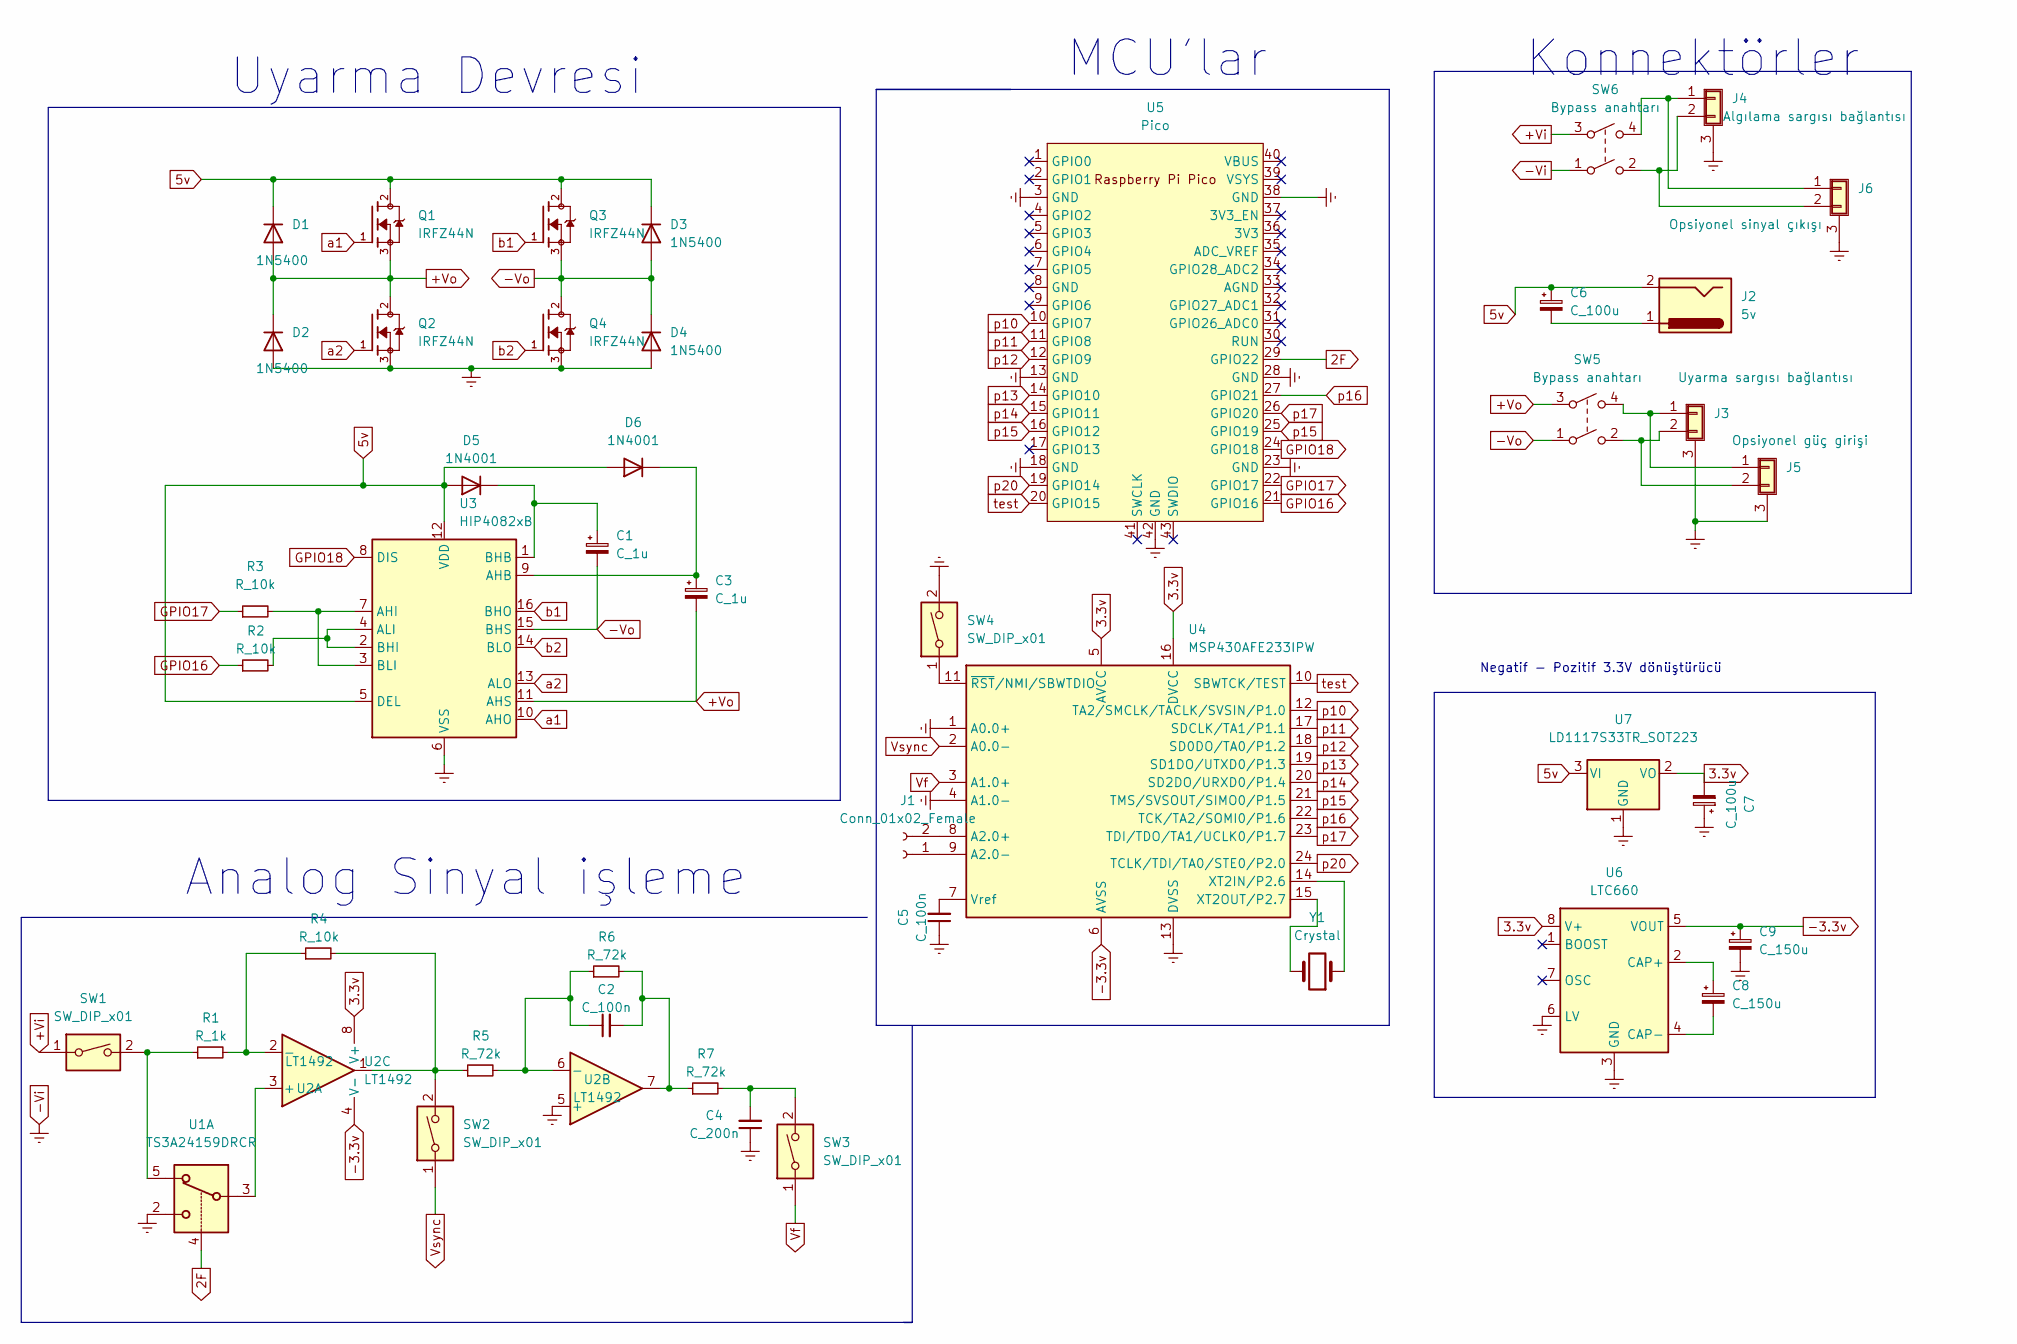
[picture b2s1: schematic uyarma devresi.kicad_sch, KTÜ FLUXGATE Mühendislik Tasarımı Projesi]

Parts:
C1, C3: C_1u; CP_Elec_3x5.3
C2: C_100n; CP_Elec_6.3x3.9
C4: C_200n; CP_Elec_6.3x3.9
C5: C_100n; CP_Elec_6.3x4.5
C6, C7: C_100u; CP_Elec_10x12.5
C8, C9: C_150u; CP_Elec_3x5.3
D1, D2, D3, D4: 1N5400; D_DO-201AD_P15.24mm_Horizontal
D5, D6: 1N4001; D_DO-41_SOD81_P10.16mm_Horizontal
J1: Conn_01x02_Female; PinHeader_1x02_P1.27mm_Vertical_SMD_Pin1Left
J2: 5v; BarrelJack_CUI_PJ-036AH-SMT_Horizontal
J3: Uyarma sargısı bağlantısı; BarrelJack_CLIFF_FC681465S_SMT_Horizontal
J4: Algılama sargısı bağlantısı; BarrelJack_CLIFF_FC681465S_SMT_Horizontal
J5: Opsiyonel güç girişi; BarrelJack_CLIFF_FC681465S_SMT_Horizontal
J6: Opsiyonel sinyal çıkışı; BarrelJack_CLIFF_FC681465S_SMT_Horizontal
Q1, Q2, Q3, Q4: IRFZ44N; TO254P1016X419X2286-3; PARTREV 09/21/10
R1: R_1k; R_Axial_DIN0204_L3.6mm_D1.6mm_P5.08mm_Horizontal
R2, R3, R4: R_10k; R_Axial_DIN0204_L3.6mm_D1.6mm_P5.08mm_Horizontal
R5, R6, R7: R_72k; R_Axial_DIN0204_L3.6mm_D1.6mm_P5.08mm_Horizontal
SW1, SW2, SW3, SW4: SW_DIP_x01; SW_DIP_SPSTx01_Slide_6.7x4.1mm_W8.61mm_P2.54mm_LowProfile
SW5, SW6: Bypass anahtarı; SW_Push_2P1T_Toggle_CK_PVA1xxH3xxxxxxV2
U1: TS3A24159DRCR; Texas_S-PVSON-N10
U2: LT1492; SO-16_3.9x9.9mm_P1.27mm
U3: HIP4082xB; SOIC-16_3.9x9.9mm_P1.27mm
U4: MSP430AFE233IPW; TSSOP-24_4.4x7.8mm_P0.65mm
U5: Pico; RPi_Pico_SMD_TH
U6: LTC660; SO-8_3.9x4.9mm_P1.27mm
U7: LD1117S33TR_SOT223; SOT-223-3_TabPin2
Y1: Crystal; R_01005_0402Metric

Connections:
2F: U1.4, U5.29 (GPIO22)
3.3v: C7.2, U2.8 (V+), U4.5 (AVCC), U4.16 (DVCC), U6.8 (V+), U7.2 (VO)
5v: C6.1, D1.1 (K), D3.1 (K), D5.2 (A), D6.2 (A), J2.2, Q1.2, Q3.2, U3.5 (DEL), U3.12 (VDD), U7.3 (VI)
+Vi: SW1.1, SW6.3
+Vo: C3.2, D1.2 (A), D2.1 (K), Q1.3, Q2.2, SW5.3, U3.11 (AHS)
-3.3v: C9.1, U2.4 (V-), U4.6 (AVSS), U6.5 (VOUT)
-Vi: C4.1, C5.1, C7.1, C9.2, D2.2 (A), D4.2 (A), J3.3 (Shield), J4.3 (Shield), J5.3 (Shield), J6.3 (Shield), Q2.3, Q4.3, SW4.2, SW6.1, U1.2, U2.5 (+), U3.6 (VSS), U4.1 (A0.0+), U4.4 (A1.0-), U4.13 (DVSS), U5.3 (GND), U5.13 (GND), U5.18 (GND), U5.23 (GND), U5.28 (GND), U5.38 (GND), U5.42 (GND), U6.3 (GND), U6.6 (LV), U7.1 (GND)
-Vo: C1.2, D3.2 (A), D4.1 (K), Q3.3, Q4.2, SW5.1, U3.15 (BHS)
GPIO16: R2.1, U5.21 (GPIO16)
GPIO17: R3.1, U5.22 (GPIO17)
GPIO18: U3.8 (DIS), U5.24 (GPIO18)
unnamed: C1.1, D5.1 (K), U3.1 (BHB)
unnamed: C2.1, R5.2, R6.1, U2.6 (-)
unnamed: C2.2, R6.2, R7.1, U2.7
unnamed: C3.1, D6.1 (K), U3.9 (AHB)
unnamed: C4.2, R7.2, SW3.2
unnamed: C5.2, U4.7 (Vref)
unnamed: C6.2, J2.1
unnamed: C8.1, U6.2 (CAP+)
unnamed: C8.2, U6.4 (CAP-)
unnamed: J1.1, U4.9 (A2.0-)
unnamed: J1.2, U4.8 (A2.0+)
unnamed: J3.1, J5.1, SW5.4
unnamed: J3.2, J5.2, SW5.2
unnamed: J4.1, J6.1, SW6.4
unnamed: J4.2, J6.2, SW6.2
unnamed: R1.1, SW1.2, U1.5
unnamed: R1.2, R4.1, U2.2 (-)
unnamed: R3.2, U3.3 (BLI), U3.7 (AHI)
unnamed: R4.2, R5.1, SW2.2, U2.1
unnamed: SW4.1, U4.11 (~RST/NMI/SBWTDIO)
unnamed: U1.3, U2.3 (+)
unnamed: R2.2, U3.2 (BHI), U3.4 (ALI)
unnamed: U4.14 (XT2IN/P2.6), Y1.1
unnamed: U4.15 (XT2OUT/P2.7), Y1.2
Vf: SW3.1, U4.3 (A1.0+)
Vsync: SW2.1, U4.2 (A0.0-)
a1: Q1.1, U3.10 (AHO)
a2: Q2.1, U3.13 (ALO)
b1: Q3.1, U3.16 (BHO)
b2: Q4.1, U3.14 (BLO)
p10: U4.12 (TA2/SMCLK/TACLK/SVSIN/P1.0), U5.10 (GPIO7)
p11: U4.17 (SDCLK/TA1/P1.1), U5.11 (GPIO8)
p12: U4.18 (SD0DO/TA0/P1.2), U5.12 (GPIO9)
p13: U4.19 (SD1DO/UTXD0/P1.3), U5.14 (GPIO10)
p14: U4.20 (SD2DO/URXD0/P1.4), U5.15 (GPIO11)
p15: U4.21 (TMS/SVSOUT/SIMO0/P1.5), U5.16 (GPIO12), U5.25 (GPIO19)
p16: U4.22 (TCK/TA2/SOMI0/P1.6), U5.27 (GPIO21)
p17: U4.23 (TDI/TDO/TA1/UCLK0/P1.7), U5.26 (GPIO20)
p20: U4.24 (TCLK/TDI/TA0/STE0/P2.0), U5.19 (GPIO14)
test: U4.10 (SBWTCK/TEST), U5.20 (GPIO15)

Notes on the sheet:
Analog Sinyal işleme
MCU'lar
Negatif - Pozitif 3.3V dönüştürücü
Uyarma Devresi
Konnektörler

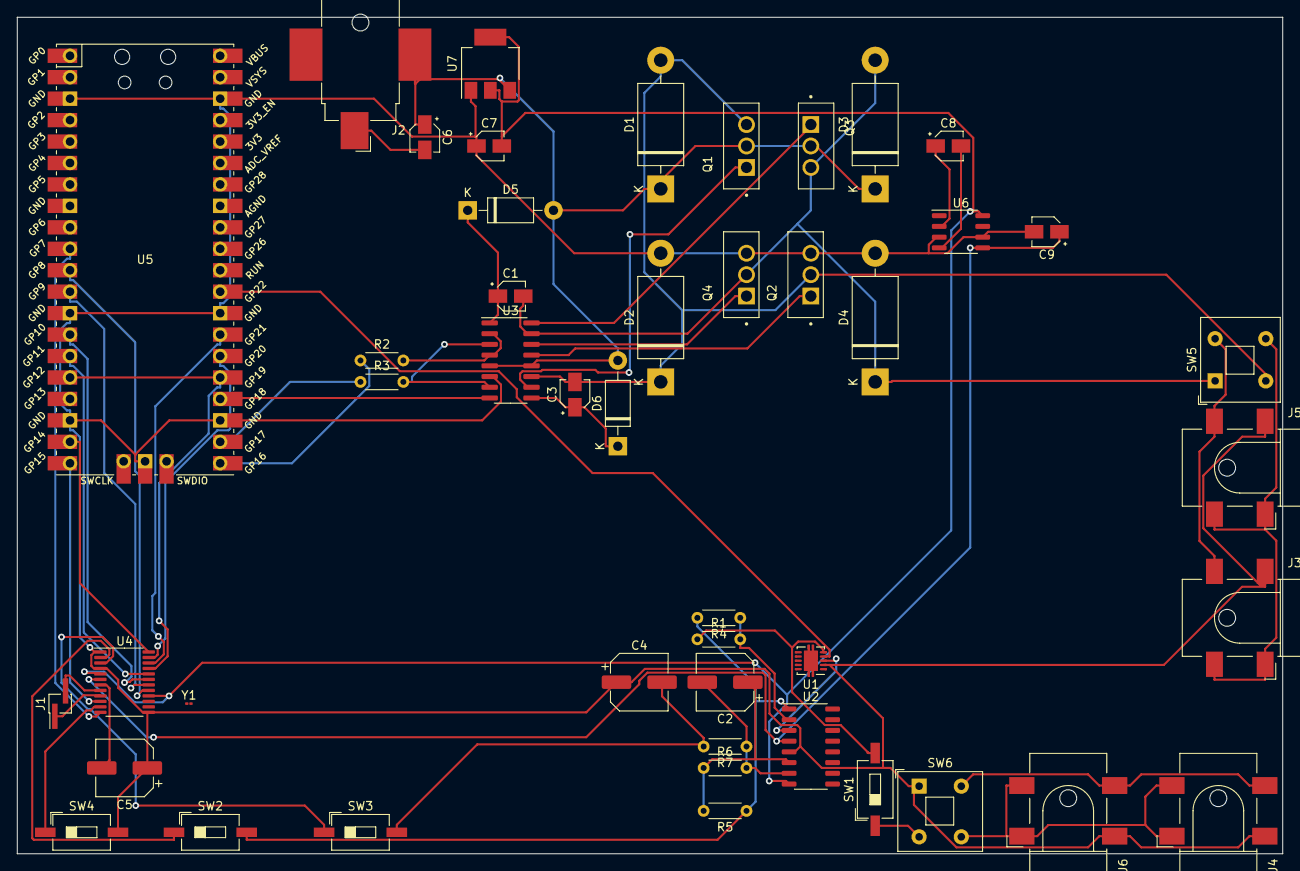
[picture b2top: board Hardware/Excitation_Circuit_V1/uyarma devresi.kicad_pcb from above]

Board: 2 copper layers, 149.9 x 99.1 mm, 46 parts (0 on the bottom side), 51 nets.

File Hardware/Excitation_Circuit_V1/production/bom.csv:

Designator,Footprint,Quantity,Value,LCSC Part #
"C1, C3",CP_Elec_3x5.3,2,C_1u,
C2,CP_Elec_6.3x3.9,1,C_100n,
C4,CP_Elec_6.3x3.9,1,C_200n,
C5,CP_Elec_6.3x4.5,1,C_100n,
"C6, C7",CP_Elec_3x5.3,2,C_100u,
"C8, C9",CP_Elec_3x5.3,2,C_150u,
"D1, D2, D3, D4",D_DO-201AD_P15.24mm_Horizontal,4,1N5400,
"D5, D6",D_DO-41_SOD81_P10.16mm_Horizontal,2,1N4001,
J1,PinHeader_1x02_P1.27mm_Vertical_SMD_Pin1Left,1,Conn_01x02_Female,
J2,BarrelJack_CUI_PJ-036AH-SMT_Horizontal,1,5v,
J3,BarrelJack_CLIFF_FC681465S_SMT_Horizontal,1,Uyarma sargısı bağlantısı,
J4,BarrelJack_CLIFF_FC681465S_SMT_Horizontal,1,Algılama sargısı bağlantısı,
J5,BarrelJack_CLIFF_FC681465S_SMT_Horizontal,1,Opsiyonel güç girişi,
J6,BarrelJack_CLIFF_FC681465S_SMT_Horizontal,1,Opsiyonel sinyal çıkışı ,
"Q1, Q2, Q3, Q4",TO254P1016X419X2286-3,4,IRFZ44N,
R1,R_Axial_DIN0204_L3.6mm_D1.6mm_P5.08mm_Horizontal,1,R_1k,
"R2, R3, R4",R_Axial_DIN0204_L3.6mm_D1.6mm_P5.08mm_Horizontal,3,R_10k,
"R5, R6, R7",R_Axial_DIN0204_L3.6mm_D1.6mm_P5.08mm_Horizontal,3,R_72k,
"SW1, SW2, SW3, SW4",SW_DIP_SPSTx01_Slide_6.7x4.1mm_W8.61mm_P2.54mm_LowProfile,4,SW_DIP_x01,
"SW5, SW6",SW_Push_2P1T_Toggle_CK_PVA1xxH3xxxxxxV2,2,Bypass anahtarı,
U1,Texas_S-PVSON-N10,1,TS3A24159DRCR,
U2,SO-16_3.9x9.9mm_P1.27mm,1,LT1492,
U3,SOIC-16_3.9x9.9mm_P1.27mm,1,HIP4082xB,
U4,TSSOP-24_4.4x7.8mm_P0.65mm,1,MSP430AFE233IPW,
U5,RPi_Pico_SMD_TH,1,Pico,
U6,SO-8_3.9x4.9mm_P1.27mm,1,LTC660,
U7,SOT-223-3_TabPin2,1,LD1117S33TR_SOT223,
Y1,01005,1,Crystal,

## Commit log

2026-05-19 Initial commit: Reorganized Fluxgate Sensor project into professional open-source structure
2026-05-19 Enriched README files with system schematic, PCB layout renders, physical board photo, and toroid core winding photos. Relocated udp_plot_pyqt.py into Software/Python_GUI_Demo
2026-05-19 Enrich documentation suite across all components with mathematical equations, physical parameters, and historical design corrections from thesis
2026-05-19 chore: ignore extracted pictures folder
